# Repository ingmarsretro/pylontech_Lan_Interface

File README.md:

# Universal LAN Board with WT32-ETH01 Module for Pylontech and more

This project introduces a universal board that can be used for various purposes. The heart of the board is a WT32-ETH01 module with an ESP32 and a LAN interface. Depending on the configuration and software, the board can fulfill different functions.

## Features

### Communication with Pylontech Solar Batteries

The board can communicate with Pylontech solar batteries (US2000, US3000c, ...) via the serial console interface. For this purpose, the software from the following repositories has been adapted from ESP8266 to ESP32:
- [Pylontech-Battery-Monitoring by irekzielinski](https://github.com/irekzielinski/Pylontech-Battery-Monitoring)
- [PylontechMonitoring by hidaba](https://github.com/hidaba/PylontechMonitoring)

Thus, the Pylontech batteries can communicate via LAN over MQTT with, for example, Homeassistant.

### Communication with Microinverters (e.g., Hoymiles)

The board can communicate with microinverters such as Hoymiles via OpenDTU software and the NRF24L01+ module:
- [OpenDTU by tbnobody](https://github.com/tbnobody/OpenDTU)

A configuration file for OpenDTU with WS32ETH 01 is included and can be adjusted if necessary. Further information for current software can be found on the OpenDTU GitHub.

### Communication via CAN or RS485

The board can communicate with various devices via CAN or RS485. Projects for this will be developed or published as needed.

## Installation

1. **Prepare Hardware:**
   - Assemble the board according to the desired functionality (e.g., NRF24L01+ module for OpenDTU or MAX3232 along with console connector for Pylontech).
   - Connect the WT32-ETH01 module to your network and the assembled function to your device (e.g., serial console interface for Pylontech batteries).

2. **Install Software:**
   - Download the appropriate software from the repositories mentioned above.
   - Adjust the configuration files to your needs.
   - Flash the software onto the WT32-ETH01 module. (In the Pylontech software script, IP addresses need to be adjusted. Use Arduino IDE for compiling.)
     To flash the software, a USB_RS232 interface is required. The "Prog" jumper must be set. The programmer is connected to the "TO-FTDI" pins.

3. **Configuration:**
   - When using with Pylontech, enter the address specified in the code in your web browser. If the connection is OK, the data of the Pylontech batteries will be displayed in the browser.
     If an MQTT server is present and correctly specified in the code, MQTT messages will be sent.
   - When using with OpenDTU, configure the network via the OpenDTU access point after flashing the firmware and load the wt32mapping.json file.
   - Ensure all connections are correct and start the system.

## Usage

Depending on configuration and software, you can use the board for various purposes:
- **Pylontech Batteries:** Monitor and control your Pylontech solar batteries via MQTT and integrate them into Homeassistant.
- **Microinverter:** Communicate with microinverters like Hoymiles via OpenDTU and monitor your solar system.
- **CAN/RS485:** Develop your own projects for communication via CAN or RS485 with various devices.

## License
free

# Universalboard mit WT32-ETH01 Modul

Dieses Projekt stellt ein Universalboard vor, das für verschiedene Zwecke verwendet werden kann. Das Herzstück des Boards ist ein WT32-ETH01 Modul mit einem ESP32 und einem LAN Interface. Je nach Bestückung und Software kann das Board verschiedene Funktionen erfüllen.

## Funktionen

### Kommunikation mit Pylontech Solarbatterien

Das Board kann mit den Solarbatterien von Pylontech (US2000, US3000c, ...) über die serielle Console-Schnittstelle kommunizieren. Dafür wurde die Software von folgenden Repositories vom ESP8266 auf den ESP32 angepasst:
- [Pylontech-Battery-Monitoring von irekzielinski](https://github.com/irekzielinski/Pylontech-Battery-Monitoring)
- [PylontechMonitoring von hidaba](https://github.com/hidaba/PylontechMonitoring)

So können die Pylontech Batterien per LAN über MQTT mit z.B. Homeassistant kommunizieren.

### Kommunikation mit Microinvertern (z.B. Hoymiles)

Das Board kann mit Microinvertern wie z.B. Hoymiles per OpenDTU Software und dem NRF24L01+ Modul kommunizieren:
- [OpenDTU von tbnobody](https://github.com/tbnobody/OpenDTU)

Ein Konfigurationsfile für openDTU mit WS32ETH 01 ist beigelegt und kann ggf angepasst werden. Weitere für aktuelle Software auf openDTU git

### Kommunikation über CAN oder RS485

Das Board kann über CAN bzw. RS485 mit beliebigen Geräten kommunizieren. Projekte dazu werden entwickelt bzw. veröffentlicht, sobald sie benötigt werden.

## Installation

1. **Hardware vorbereiten:**
   - Bestücke das Board je nach gewünschter Funktionalität (z.B. NRF24L01+ Modul für OpenDTU oder MAX3232 samt Console Conector für Pylontech)
   - Verbinde das WT32-ETH01 Modul mit deinem Netzwerk und die bestückte Funtkion mit deinem Gerät (z.B. serielle Console-Schnittstelle für Pylontech Batterien).

2. **Software installieren:**
   - Lade die entsprechende Software aus den oben genannten Repositories herunter. 
   - Passe die Konfigurationsdateien an deine Bedürfnisse an. 
   - Flashe die Software auf das WT32-ETH01 Modul. (im Pylontech Softwarescript müssen die IP Adressen angepasst werden. zum kompilieren z.b. Adruino IDE verwenden)
     Zum flashen der Software ist ein USB_RS232 Interface notwendig. Der Jumper "Prog" muss gesetzt sein. Der Programmer wird an den Pins "TO-FTDI" angeschlossen

3. **Konfiguration:**
   - bei Verwendung mit Pylontech im Webbrowser die im code eingegeben Adresse eingeben. Ist die Verbindung OK werden die Daten der Pylontech Batterien im Browser angezeigt.
     Ist der MQTT Server vorhanden und im code richtig angegeben dann werden die mqtt messages gesendet
   - bei Verwednung mit openDTU ist nach dem Flashen der Firmware über den openDTU accesspoint das Netzwerk zu konfigurieren und das wt32mapping.json file zu laden.
   - Stelle sicher, dass alle Verbindungen korrekt sind und starte das System.

## Nutzung

Je nach Bestückung und Software kannst du das Board für verschiedene Zwecke nutzen:
- **Pylontech Batterien:** Überwache und steuere deine Pylontech Solarbatterien über MQTT und integriere sie in Homeassistant.
- **Microinverter:** Kommuniziere mit Microinvertern wie Hoymiles über OpenDTU und überwache deine Solaranlage.
- **CAN/RS485:** Entwickle eigene Projekte zur Kommunikation über CAN oder RS485 mit verschiedenen Geräten.

## Lizenz
free

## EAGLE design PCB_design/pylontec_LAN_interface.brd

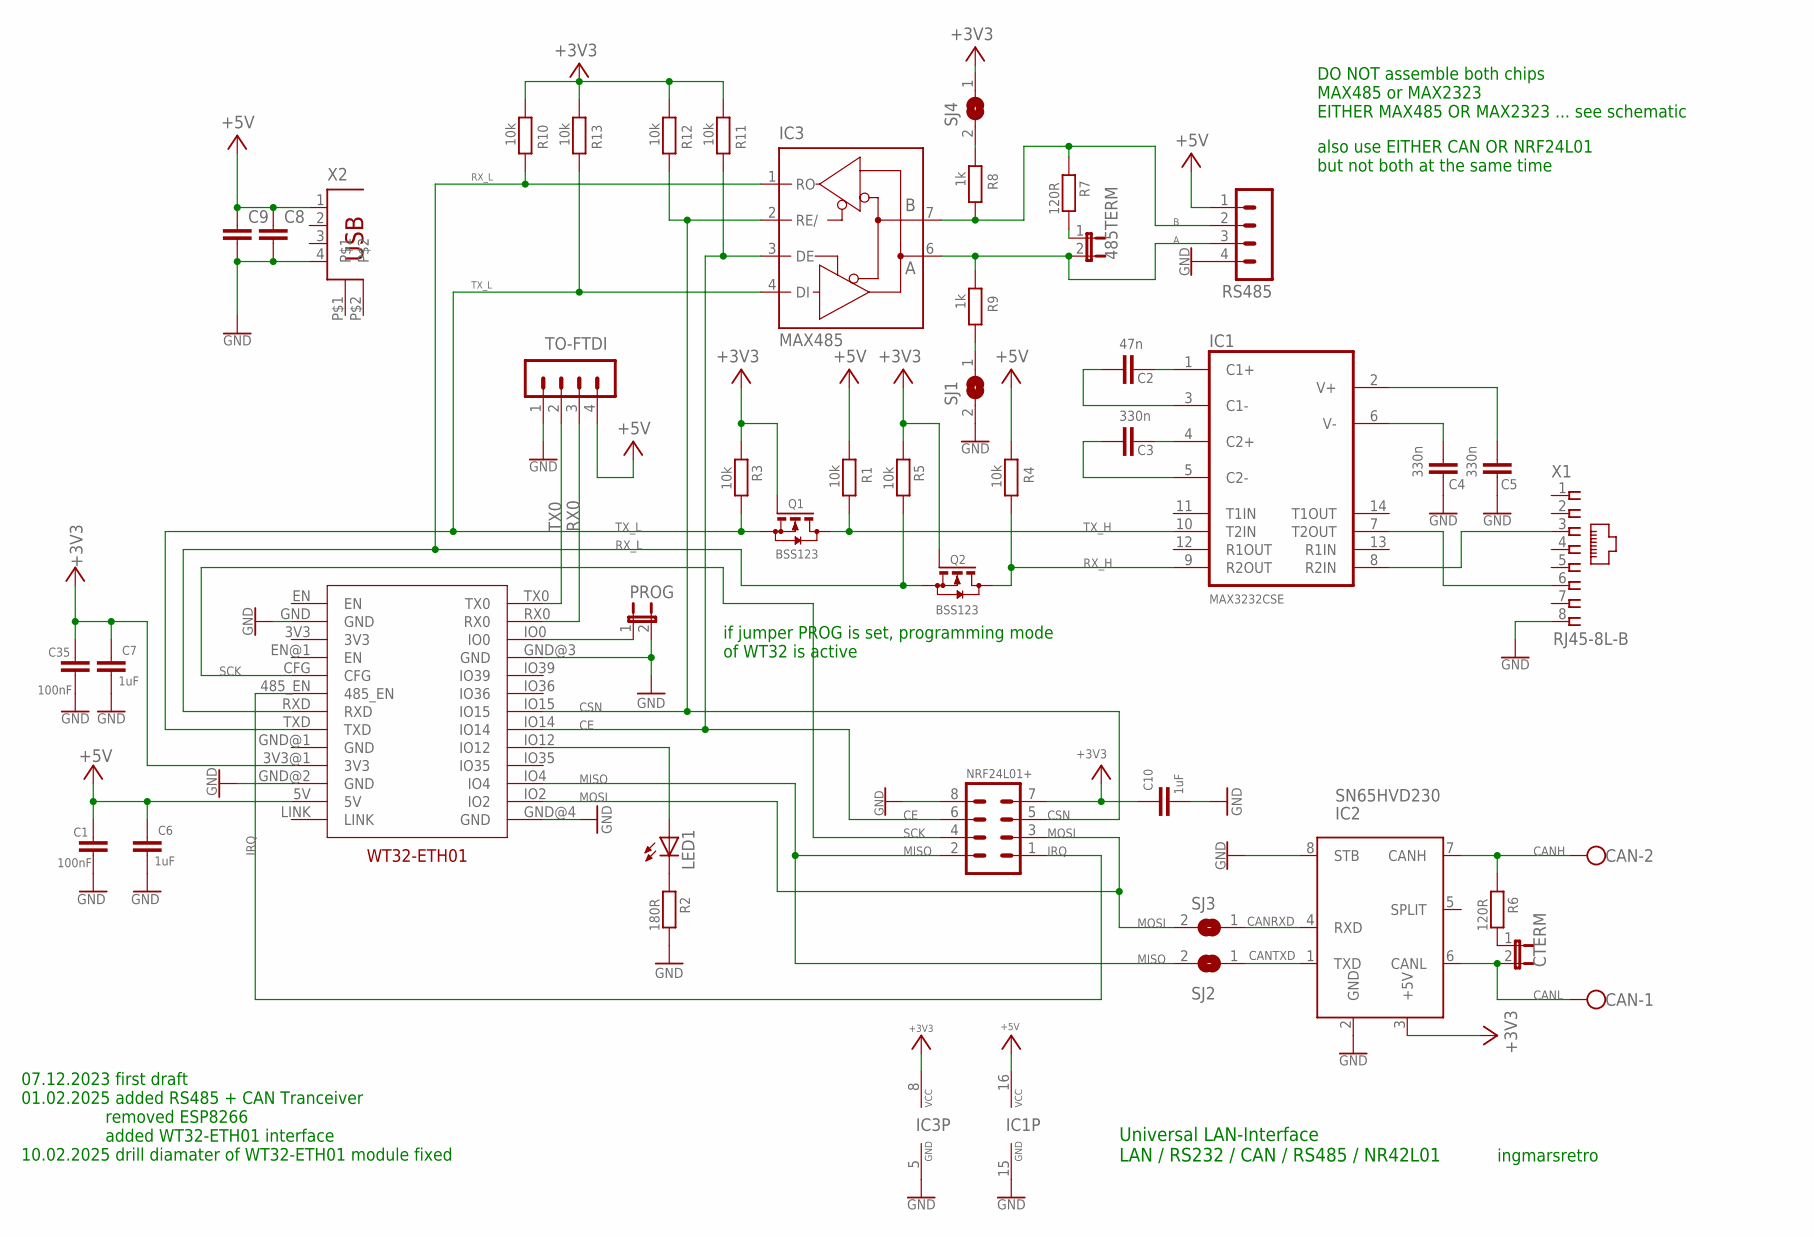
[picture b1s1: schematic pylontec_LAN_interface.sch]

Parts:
485TERM: JP1E; JP1
C1, C35: 100nF; C0805
C2: 47n; C0805
C3, C4, C5: 330n; C0805
C6, C7, C10: 1uF; C1210
C8, C9: C-EUC1210; C1210
CAN: W237-102
CTERM: JP1E; JP1
IC1: MAX3232CSE; SO16
IC2: SN65HVD230; SO8
IC3: MAX485; SO08
LED1: LED_LEDCHIPLED_0805; LED_CHIPLED_0805
NRF24L01+: MA04-2
PROG: JP1E; JP1
Q1, Q2: BSS123; SOT23
R1, R3, R4, R5, R10, R11, R12, R13: 10k; R0805
R2: 180R; R0805
R6, R7: 120R; R0805
R8, R9: 1k; R0805
RS485: MA04-1
SJ1, SJ2, SJ3, SJ4: SJ
TO-FTDI: MA04-1
U$2: WT32-ETH01
X1: RJ45-8L-B; RJ45-NO-SHIELD
X2: SMARTPRJ_PN61729

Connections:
+3V3: C7.1, C10.1, C35.2, IC2.3 (+5V), IC3.8 (VCC), NRF24L01+.7, Q1.1 (G), Q2.1 (G), R3.1, R5.1, R10.1, R11.1, R12.1, R13.1, SJ4.1, U$2.3V3@1 (3V3)
+5V: C1.2, C6.1, C8.1, C9.1, IC1.16 (VCC), R1.1, R4.1, RS485.1, TO-FTDI.4, U$2.5V, X2.1
A: 485TERM.2, IC3.6 (A), R9.1, RS485.3
B: IC3.7 (B), R7.1, R8.2, RS485.2
CANH: CAN.2, IC2.7 (CANH), R6.1
CANL: CAN.1, CTERM.2, IC2.6 (CANL)
CANRXD: IC2.4 (RXD), SJ3.1
CANTXD: IC2.1 (TXD), SJ2.1
CE: IC3.3 (DE), NRF24L01+.6, R11.2, U$2.IO14
CSN: IC3.2 (RE/), NRF24L01+.5, R12.2, U$2.IO15
GND: C1.1, C4.2, C5.2, C6.2, C7.2, C8.2, C9.2, C10.2, C35.1, IC1.15 (GND), IC2.2 (GND), IC2.8 (STB), IC3.5 (GND), NRF24L01+.8, PROG.2, R2.2, RS485.4, SJ1.2, TO-FTDI.1, U$2.GND, U$2.GND@2 (GND), U$2.GND@3 (GND), U$2.GND@4 (GND), X1.8, X2.4
IRQ: NRF24L01+.1, U$2.485_EN
MISO: NRF24L01+.2, SJ2.2, U$2.IO4
MOSI: NRF24L01+.3, SJ3.2, U$2.IO2
unnamed: IC1.8 (R2IN), X1.3
unnamed: C2.1, IC1.1 (C1+)
unnamed: PROG.1, U$2.IO0
unnamed: C2.2, IC1.3 (C1-)
unnamed: C3.1, IC1.4 (C2+)
unnamed: C3.2, IC1.5 (C2-)
unnamed: C4.1, IC1.6 (V-)
unnamed: C5.1, IC1.2 (V+)
unnamed: IC1.7 (T2OUT), X1.6
unnamed: LED1.A, U$2.IO12
unnamed: LED1.C, R2.1
unnamed: 485TERM.1, R7.2
unnamed: CTERM.1, R6.2
unnamed: R9.2, SJ1.1
unnamed: R8.1, SJ4.2
RX0: TO-FTDI.3, U$2.RX0
RX_H: IC1.9 (R2OUT), Q2.3 (D), R4.2
RX_L: IC3.1 (RO), Q2.2 (S), R5.2, R10.2, U$2.RXD
SCK: NRF24L01+.4, U$2.CFG
TX0: TO-FTDI.2, U$2.TX0
TX_H: IC1.10 (T2IN), Q1.3 (D), R1.2
TX_L: IC3.4 (DI), Q1.2 (S), R3.2, R13.2, U$2.TXD

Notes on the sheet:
ingmarsretro
Universal LAN-Interface LAN / RS232 / CAN / RS485 / NR42L01
07.12.2023 first draft 01.02.2025 added RS485 + CAN Tranceiver removed ESP8266 added WT32-ETH01 interface 10.02.2025 drill diamater of WT32-ETH01 module fixed
if jumper PROG is set, programming mode of WT32 is active
DO NOT assemble both chips MAX485 or MAX2323 EITHER MAX485 OR MAX2323 ... see schematic
also use EITHER CAN OR NRF24L01 but not both at the same time

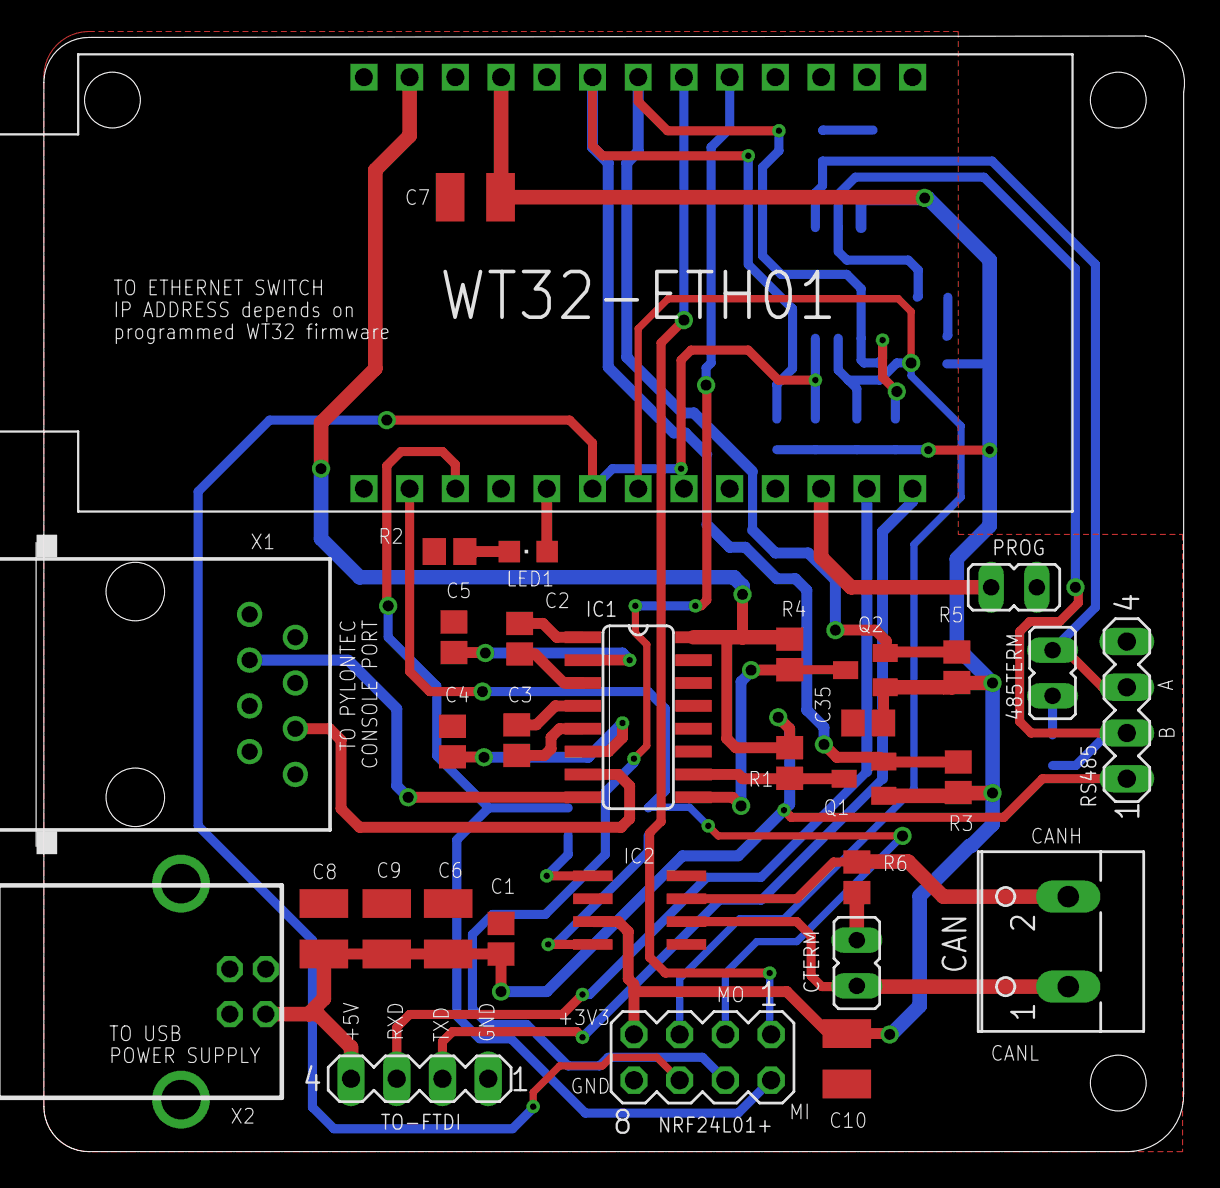
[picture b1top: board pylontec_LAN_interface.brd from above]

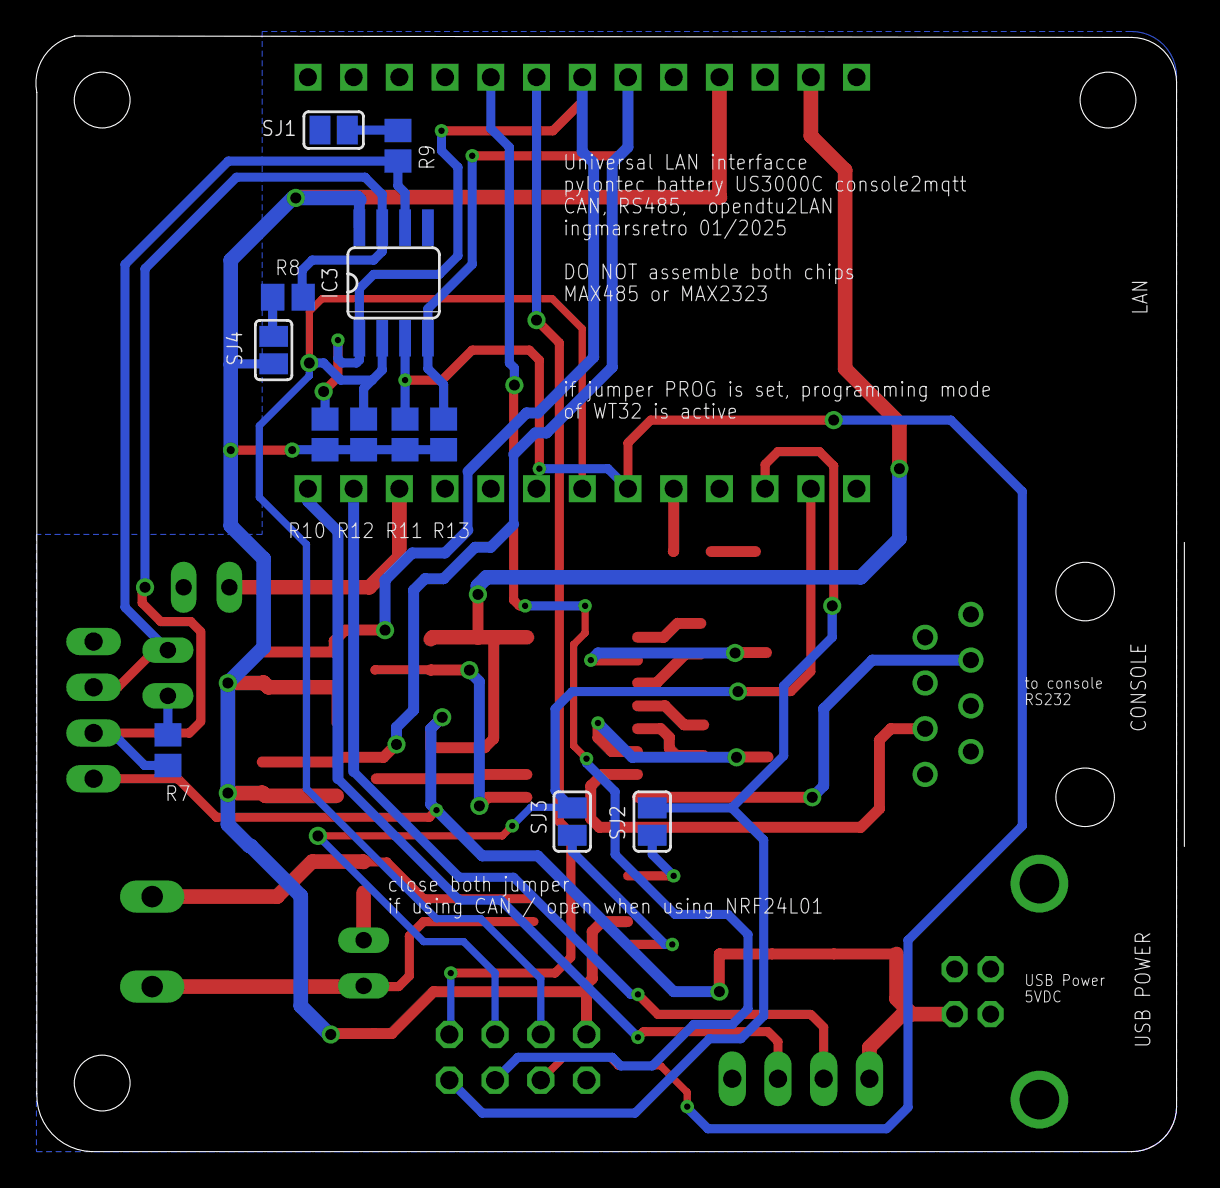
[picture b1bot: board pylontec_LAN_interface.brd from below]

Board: 2 copper layers, 63.4 x 62.0 mm, 44 parts (12 on the bottom side), 36 nets.

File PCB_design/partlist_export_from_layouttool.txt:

Partlist

Exported from pylontec_LAN_interface.sch at 06.03.2025 11:38


Assembly variant: 

Part      Value          Device              Package          Library                 Sheet

485TERM                  JP1E                JP1              jumper                  1
C1        100nF          C-EUC0805           C0805            resistor                1
C2        47n            C-EUC0805           C0805            resistor                1
C3        330n           C-EUC0805           C0805            resistor                1
C4        330n           C-EUC0805           C0805            resistor                1
C5        330n           C-EUC0805           C0805            resistor                1
C6        1uF            C-EUC1210           C1210            rcl                     1
C7        1uF            C-EUC1210           C1210            rcl                     1
C8                       C-EUC1210           C1210            rcl                     1
C9                       C-EUC1210           C1210            rcl                     1
C10       1uF            C-EUC1210           C1210            rcl                     1
C35       100nF          C-EUC0805           C0805            resistor                1
CAN                      W237-102            W237-102         con-wago-500            1
CTERM                    JP1E                JP1              jumper                  1
IC1       MAX3232CSE     MAX3232CSE          SO16             maxim                   1
IC2       SN65HVD230     TJA1040             SO8              nxp                     1
IC3       MAX485         MAX481CSA           SO08             maxim                   1
LED1                     LED_LEDCHIPLED_0805 LED_CHIPLED_0805 arduino_Uno_ref         1
NRF24L01+                MA04-2              MA04-2           con-lstb                1
PROG                     JP1E                JP1              jumper                  1
Q1        BSS123         BSS123              SOT23            transistor-small-signal 1
Q2        BSS123         BSS123              SOT23            transistor-small-signal 1
R1        10k            R-EU_R0805          R0805            resistor                1
R2        180R           R-EU_R0805          R0805            resistor                1
R3        10k            R-EU_R0805          R0805            resistor                1
R4        10k            R-EU_R0805          R0805            resistor                1
R5        10k            R-EU_R0805          R0805            resistor                1
R6        120R           R-EU_R0805          R0805            resistor                1
R7        120R           R-EU_R0805          R0805            resistor                1
R8        1k             R-EU_R0805          R0805            resistor                1
R9        1k             R-EU_R0805          R0805            resistor                1
R10       10k            R-EU_R0805          R0805            resistor                1
R11       10k            R-EU_R0805          R0805            resistor                1
R12       10k            R-EU_R0805          R0805            resistor                1
R13       10k            R-EU_R0805          R0805            resistor                1
RS485                    MA04-1              MA04-1           con-lstb                1
SJ1                      SJ                  SJ               jumper                  1
SJ2                      SJ                  SJ               jumper                  1
SJ3                      SJ                  SJ               jumper                  1
SJ4                      SJ                  SJ               jumper                  1
TO-FTDI                  MA04-1              MA04-1           con-lstb                1
U$2       WT32-ETH01     WT32-ETH01          WT32-ETH01       WT32-ETH01              1
X1        RJ45-8L-B      RJ45-8L-B           RJ45-NO-SHIELD   con-tycoelectronics     1
X2                       SMARTPRJ_PN61729    SMARTPRJ_PN61729 arduino_Uno_ref         1

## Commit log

2025-03-06 Add files via upload
    PCB-layout and PCB-schematics
2025-03-06 Add files via upload
    these are the .stl files for a case-box for the pcb with different setup possibilities
